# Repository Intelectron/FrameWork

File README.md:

# Intelectron FrameWork
Opens Source Arduino Compatible Platform for Industrial Control Systems

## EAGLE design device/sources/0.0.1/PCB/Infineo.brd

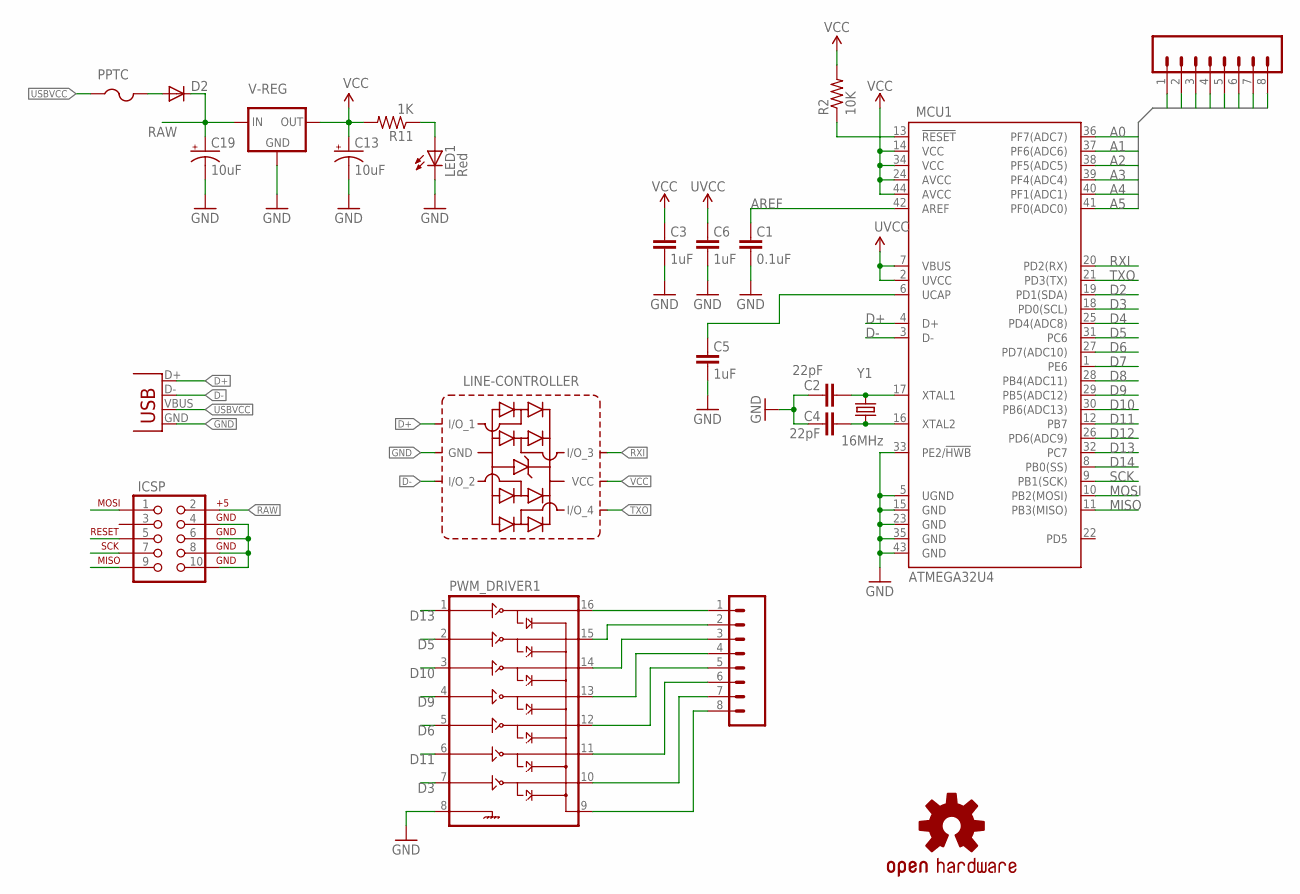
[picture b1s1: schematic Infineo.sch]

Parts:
C1: 0.1uF; 0603-CAP
C2, C4: 22pF; 0603-CAP
C3, C5, C6: 1uF; 0603-CAP
C13, C19: 10uF; EIA3216
D2: DIODESOD; SOD-323
ICSP: AVR_SPI_PROG2LOCK; 2X5-SHROUDED_LOCK
JP1, JP3: M08LOCK_LONGPADS; 1X08_LOCK_LONGPADS
LED1: Red; LED-0603
LINE-CONTROLLER: SP3004_04XTG; SOT-563
MCU1: ATMEGA32U4; SPARKFUN-DIGITALIC_TQFP44
PPTC: PTCFUSE-1206; R1206
PWM_DRIVER1: IC_ULN2003-TSSOP-16; TSSOP-16
R2: 10K; 0603-RES
R11: 1K; 0603-RES
U$3: OSHW-LOGOS; OSHW-LOGO-S
V-REG: LM1117; SOT223
X3: USB-B-H
Y1: 16MHz; HC49UP

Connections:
3.3V: C3.2
!RESET: ICSP.5, MCU1.13 (!RESET), R2.1
A0: JP1.2, MCU1.36 (PF7(ADC7))
A1: JP1.3, MCU1.37 (PF6(ADC6))
A2: JP1.4, MCU1.38 (PF5(ADC5))
A3: JP1.5, MCU1.39 (PF4(ADC4))
A4: JP1.6, MCU1.40 (PF1(ADC1))
A5: JP1.7, MCU1.41 (PF0(ADC0))
AREF: C1.2, MCU1.42 (AREF)
D2: MCU1.19 (PD1(SDA))
D3: MCU1.18 (PD0(SCL)), PWM_DRIVER1.7 (7B)
D4: MCU1.25 (PD4(ADC8))
D5: MCU1.31 (PC6), PWM_DRIVER1.2 (2B)
D6: MCU1.27 (PD7(ADC10)), PWM_DRIVER1.5 (5B)
D7: MCU1.1 (PE6)
D8: MCU1.28 (PB4(ADC11))
D9: MCU1.29 (PB5(ADC12)), PWM_DRIVER1.4 (4B)
D10: MCU1.30 (PB6(ADC13)), PWM_DRIVER1.3 (3B)
D11: MCU1.12 (PB7), PWM_DRIVER1.6 (6B)
D12: MCU1.26 (PD6(ADC9))
D13: MCU1.32 (PC7), PWM_DRIVER1.1 (1B)
D14: ICSP.9, MCU1.11 (PB3(MISO))
D+: LINE-CONTROLLER.I/O_1, MCU1.4 (D+), X3.D+
D-: LINE-CONTROLLER.I/O_2, MCU1.3 (D-), X3.D-
GND: C1.1, C2.2, C3.1, C4.2, C5.1, C6.1, C13.C (-), C19.C (-), ICSP.4, ICSP.6, ICSP.8, ICSP.10, JP1.8, LED1.C, LINE-CONTROLLER.GND, MCU1.5 (UGND), MCU1.15 (GND), MCU1.23 (GND), MCU1.33 (PE2/!HWB), MCU1.35 (GND), MCU1.43 (GND), PWM_DRIVER1.8 (GND), V-REG.1 (GND), X3.GND
MISO: MCU1.8 (PB0(SS))
MOSI: ICSP.1, MCU1.10 (PB2(MOSI))
unnamed: C4.1, MCU1.16 (XTAL2), Y1.1
unnamed: C2.1, MCU1.17 (XTAL1), Y1.2
unnamed: D2.2 (A), PPTC.2
unnamed: C5.2, MCU1.6 (UCAP)
unnamed: JP3.1, PWM_DRIVER1.16 (1C)
unnamed: JP3.2, PWM_DRIVER1.15 (2C)
unnamed: JP3.3, PWM_DRIVER1.14 (3C)
unnamed: JP3.4, PWM_DRIVER1.13 (4C)
unnamed: JP3.5, PWM_DRIVER1.12 (5C)
unnamed: JP3.6, PWM_DRIVER1.11 (6C)
unnamed: JP3.7, PWM_DRIVER1.10 (7C)
unnamed: JP3.8, PWM_DRIVER1.9 (COM)
unnamed: LED1.A, R11.1
RAW: C19.A (+), D2.1 (C), ICSP.2, V-REG.3 (IN)
RXI: LINE-CONTROLLER.I/O_3, MCU1.20 (PD2(RX))
SCK: ICSP.7, MCU1.9 (PB1(SCK))
TXO: LINE-CONTROLLER.I/O_4, MCU1.21 (PD3(TX))
USBVCC: PPTC.1, X3.VBUS
UVCC: C6.2, MCU1.2 (UVCC), MCU1.7 (VBUS)
VCC: C13.A (+), JP1.1, LINE-CONTROLLER.VCC, MCU1.14 (VCC), MCU1.24 (AVCC), MCU1.34 (VCC), MCU1.44 (AVCC), R2.2, R11.2, V-REG.2 (OUT)

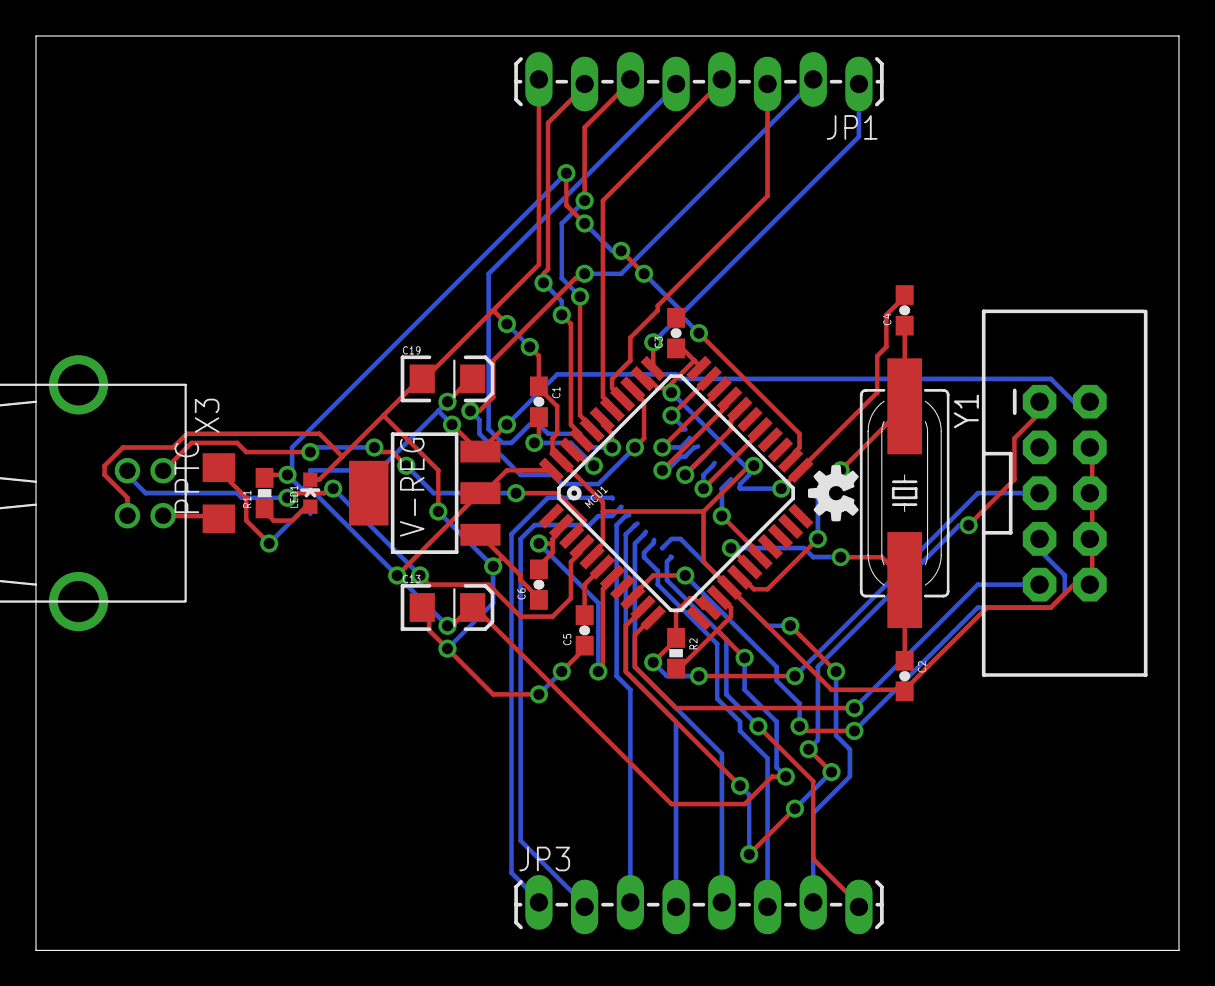
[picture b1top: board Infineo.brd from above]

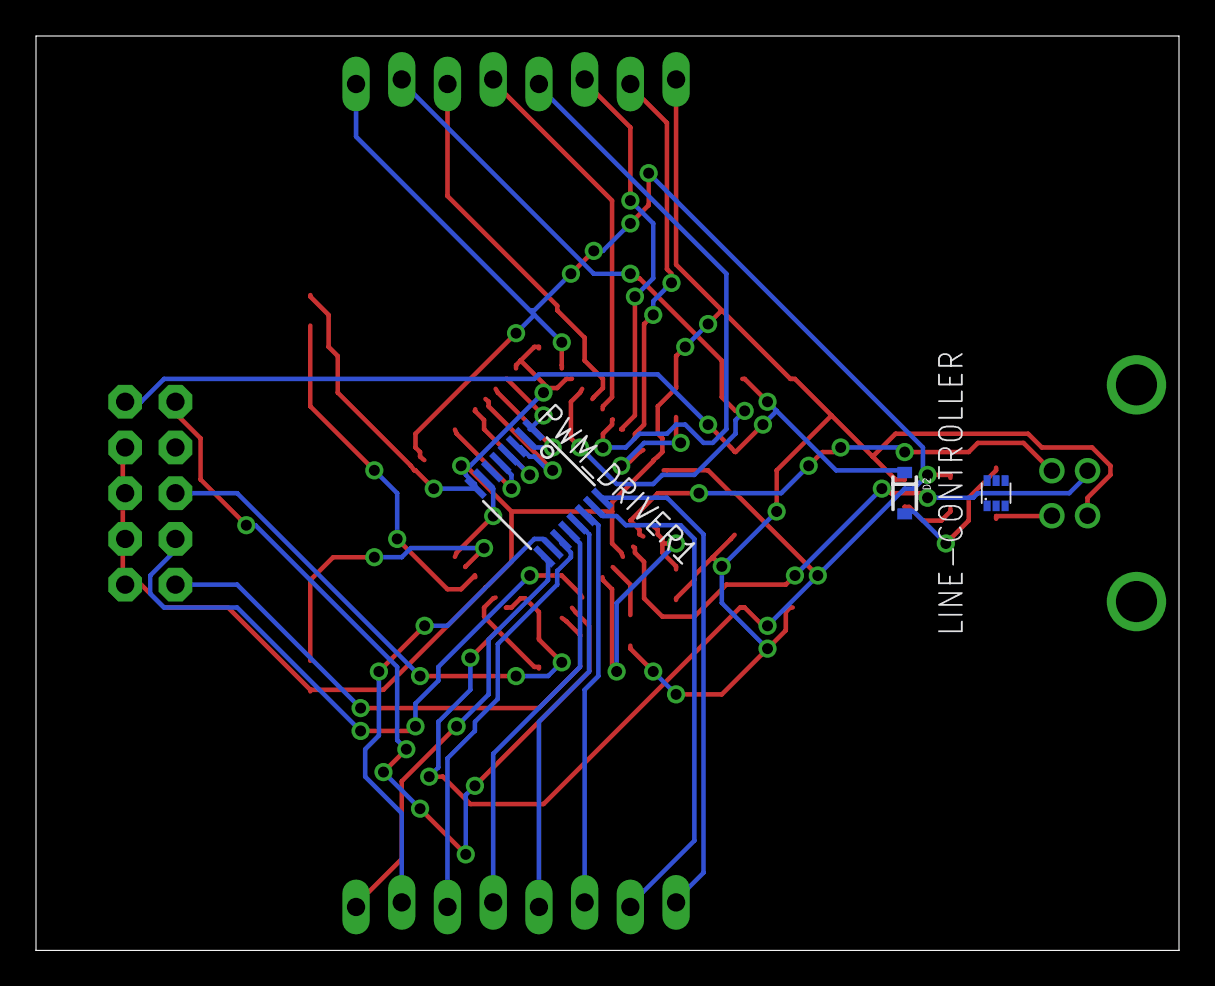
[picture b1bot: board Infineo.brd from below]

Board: 2 copper layers, 63.5 x 50.8 mm, 23 parts (3 on the bottom side), 40 nets.

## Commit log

2017-04-03 Readme v0.0.1
    Added readme file
2017-04-03 Driver v0.0.1
    Added driver sources and compiled binaries
2017-04-03 Module v0.0.1
    Added module sources and compiled binaries
2017-04-04 Update LICENSE
    Updated CC-BY-ND _v_**3.0** to CC-BY-**NC**-ND **4.0**
2017-04-08 Device v0.0.1
    Device PCB files added

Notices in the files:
parts and their libraries:
SparkFun-Retired: Licensing:Creative Commons ShareAlike 4.0 International - https://creativecommons.org/licenses/by-sa/4.0
SparkFun-Connectors: Licensing: CC v3.0 Share-Alike You are welcome to use this library for commercial purposes.
